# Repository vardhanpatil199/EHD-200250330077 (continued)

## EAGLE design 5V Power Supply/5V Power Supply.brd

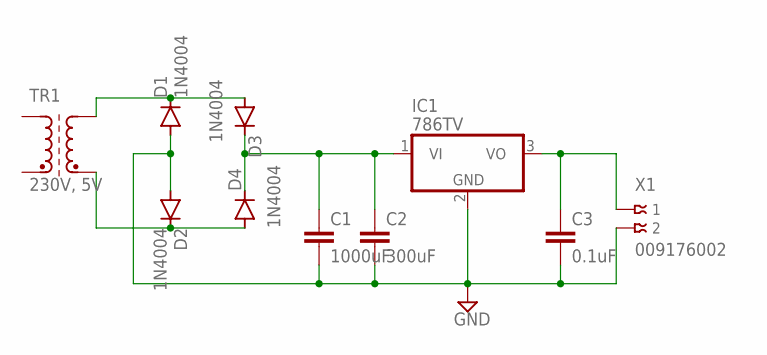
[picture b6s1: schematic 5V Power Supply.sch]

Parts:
C1: 1000uF; C2.5-2
C2: 300uF; C2.5-2
C3: 0.1uF; C2.5-2
D1, D2, D3, D4: 1N4004; DO41-10
IC1: 786TV; TO220V
TR1: 230V, 5V; SM-T4
X1: 009176002

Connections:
GND: C1.2, C2.2, C3.2, D1.A, D2.A, IC1.2 (GND), X1.2
unnamed: D1.C, D3.A, TR1.5 (A2)
unnamed: D2.C, D4.A, TR1.4 (E2)
unnamed: C1.1, C2.1, D3.C, D4.C, IC1.1 (VI)
VCC: C3.1, IC1.3 (VO), X1.1

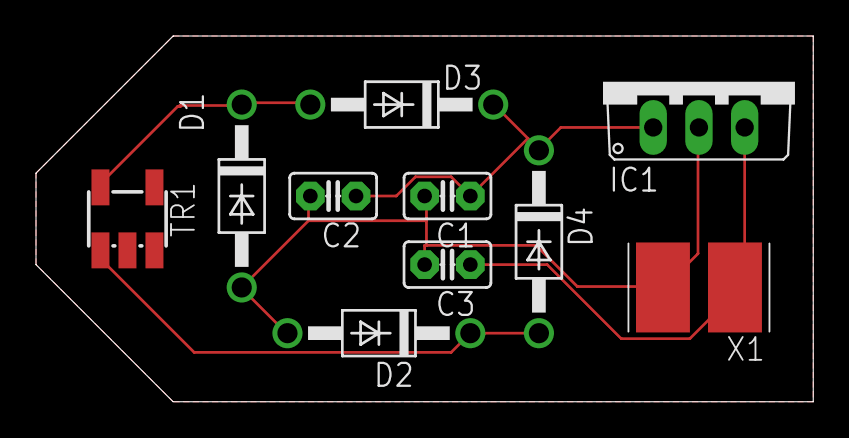
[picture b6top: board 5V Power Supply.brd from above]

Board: 2 copper layers, 43.2 x 20.3 mm, 10 parts (0 on the bottom side), 5 nets.
